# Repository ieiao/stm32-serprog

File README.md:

# STM32-serprog

## 概述

本项目是flashrom工具serprog编程器的一种实现，参考了[dword1511/stm32-vserprog](https://github.com/dword1511/stm32-vserprog)中v3版本电路原理图，增加了电平转换芯片用来同时支持1.8V和3.3V的spi flash，可以直接使用该仓库中的代码，经测试可以正常工作，PCB效果图如下。

## Changelog

* v0.2 (该版本未发板验证，不过原理图整体改动不大，应该没有问题)
    * 删除了多余的测试点
    * 将txs0108修改为txs0104/txb0104，节约成本

* v0.1
    * 第一个版本，已打板验证

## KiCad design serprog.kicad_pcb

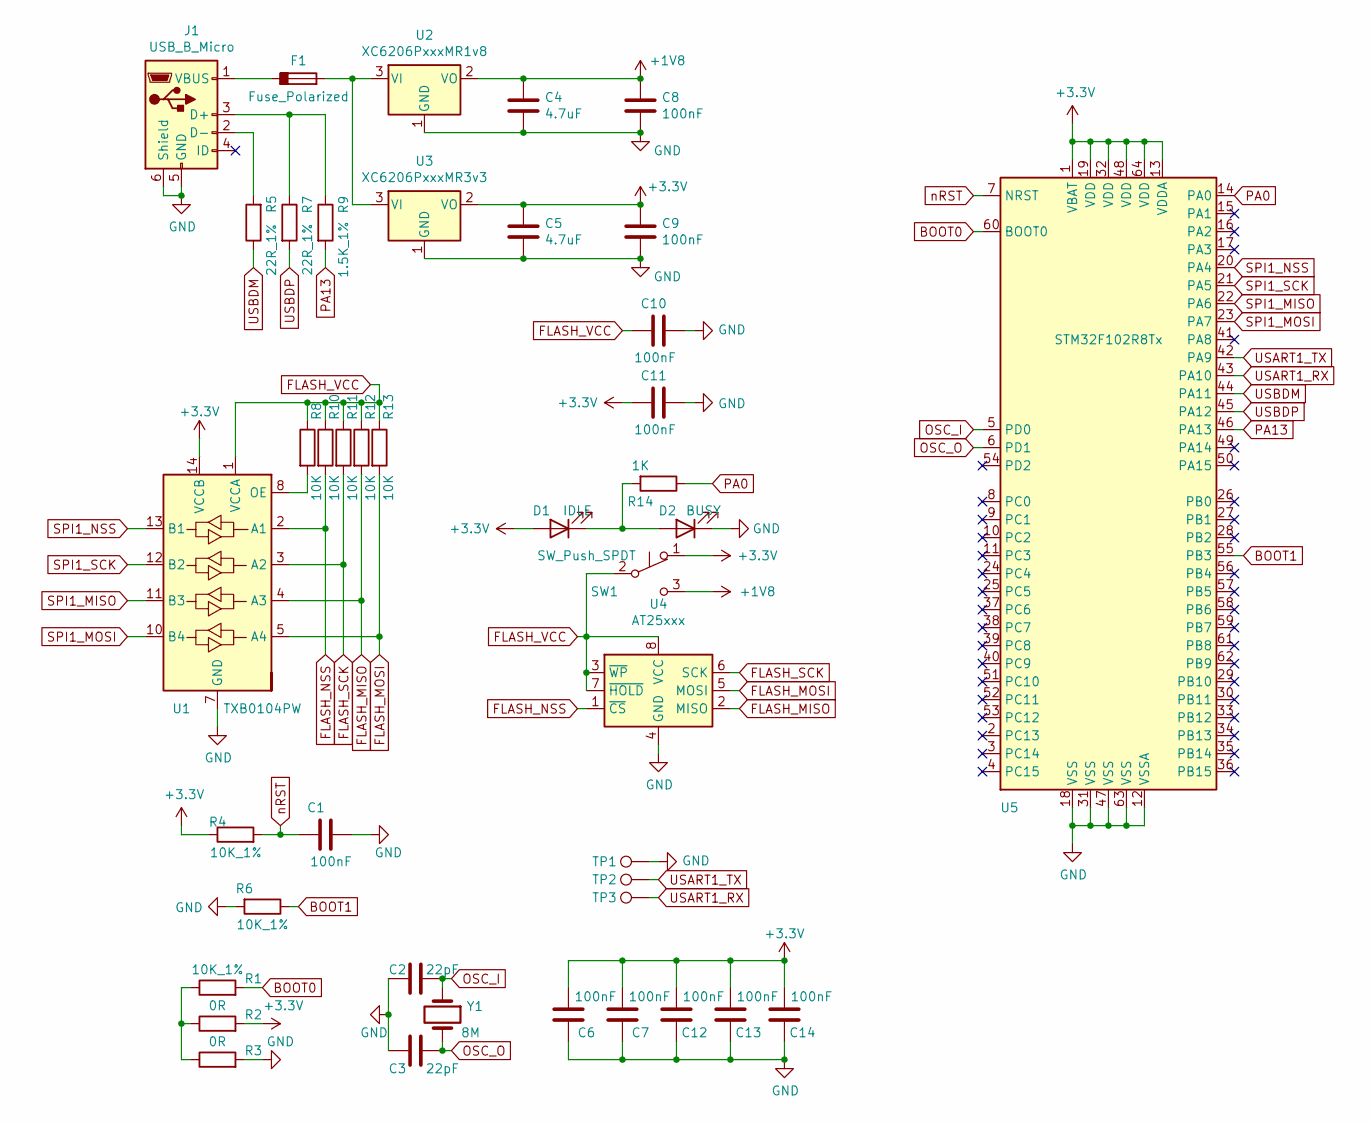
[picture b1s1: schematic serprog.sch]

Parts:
C1, C6, C7, C8, C9, C10, C11, C12, C13, C14: 100nF; C_0603_1608Metric
C2, C3: 22pF; C_0603_1608Metric
C4, C5: 4.7uF; C_0603_1608Metric
D1: IDLE; LED_0603_1608Metric
D2: BUSY; LED_0603_1608Metric
F1: Fuse_Polarized; Fuse_1210_3225Metric
J1: USB_B_Micro; USB_Micro-B_Molex-105017-0001
R1, R4, R6: 10K_1%; R_0603_1608Metric
R2, R3: 0R; R_0603_1608Metric
R5, R7: 22R_1%; R_0603_1608Metric
R8, R10, R11, R12, R13: 10K; R_0603_1608Metric
R9: 1.5K_1%; R_0603_1608Metric
R14: 1K; R_0603_1608Metric
SW1: SW_Push_SPDT; SW-DIP-3
TP1: GND; TestPoint_Pad_D1.0mm
TP2: TX; TestPoint_Pad_D1.0mm
TP3: RX; TestPoint_Pad_D1.0mm
U1: TXB0104PW; TSSOP-14_4.4x5mm_P0.65mm
U2: XC6206PxxxMR1v8; SOT-23
U3: XC6206PxxxMR3v3; SOT-23
U4: AT25xxx; DIP-8_W7.62mm
U5: STM32F102R8Tx; LQFP-64_10x10mm_P0.5mm
Y1: 8M; Crystal_HC49-4H_Vertical

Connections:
+1V8: C4.1, C8.1, SW1.3 (C), U2.2 (VO)
+3V3: C5.1, C6.1, C7.1, C9.1, C11.1, C12.1, C13.1, C14.1, D1.2 (A), R2.2, R4.1, SW1.1 (A), U1.14 (VCCB), U3.2 (VO), U5.1 (VBAT), U5.13 (VDDA), U5.19 (VDD), U5.32 (VDD), U5.48 (VDD), U5.64 (VDD)
BOOT0: R1.2, U5.60 (BOOT0)
BOOT1: R6.1, U5.55 (PB3)
FLASH_MISO: R12.2, U1.4 (A3), U4.2 (MISO)
FLASH_MOSI: R13.2, U1.5 (A4), U4.5 (MOSI)
FLASH_NSS: R10.2, U1.2 (A1), U4.1 (~CS)
FLASH_SCK: R11.2, U1.3 (A2), U4.6 (SCK)
FLASH_VCC: C10.1, R8.1, R10.1, R11.1, R12.1, R13.1, SW1.2 (B), U1.1 (VCCA), U4.3 (~WP), U4.7 (~HOLD), U4.8 (VCC)
GND: C1.2, C2.2, C3.2, C4.2, C5.2, C6.2, C7.2, C8.2, C9.2, C10.2, C11.2, C12.2, C13.2, C14.2, D2.1 (K), J1.5 (GND), J1.6 (Shield), R3.2, R6.2, TP1.1, U1.7 (GND), U2.1 (GND), U3.1 (GND), U4.4 (GND), U5.12 (VSSA), U5.18 (VSS), U5.31 (VSS), U5.47 (VSS), U5.63 (VSS); also elsewhere on the board
unnamed: D1.1 (K), D2.2 (A), R14.2
unnamed: F1.1, J1.1 (VBUS)
unnamed: F1.2, U2.3 (VI), U3.3 (VI)
unnamed: J1.2 (D-), R5.2
unnamed: J1.3 (D+), R7.1, R9.1
unnamed: R1.1, R2.1, R3.1
unnamed: R8.2, U1.8 (OE)
OSC_I: C2.1, U5.5 (PD0), Y1.1
OSC_O: C3.1, U5.6 (PD1), Y1.2
PA0: R14.1, U5.14 (PA0)
PA13: R9.2, U5.46 (PA13)
SPI1_MISO: U1.11 (B3), U5.22 (PA6)
SPI1_MOSI: U1.10 (B4), U5.23 (PA7)
SPI1_NSS: U1.13 (B1), U5.20 (PA4)
SPI1_SCK: U1.12 (B2), U5.21 (PA5)
USART1_RX: TP3.1, U5.43 (PA10); also elsewhere on the board
USART1_TX: TP2.1, U5.42 (PA9); also elsewhere on the board
USBDM: R5.1, U5.44 (PA11)
USBDP: R7.2, U5.45 (PA12)
nRST: C1.1, R4.2, U5.7 (NRST)

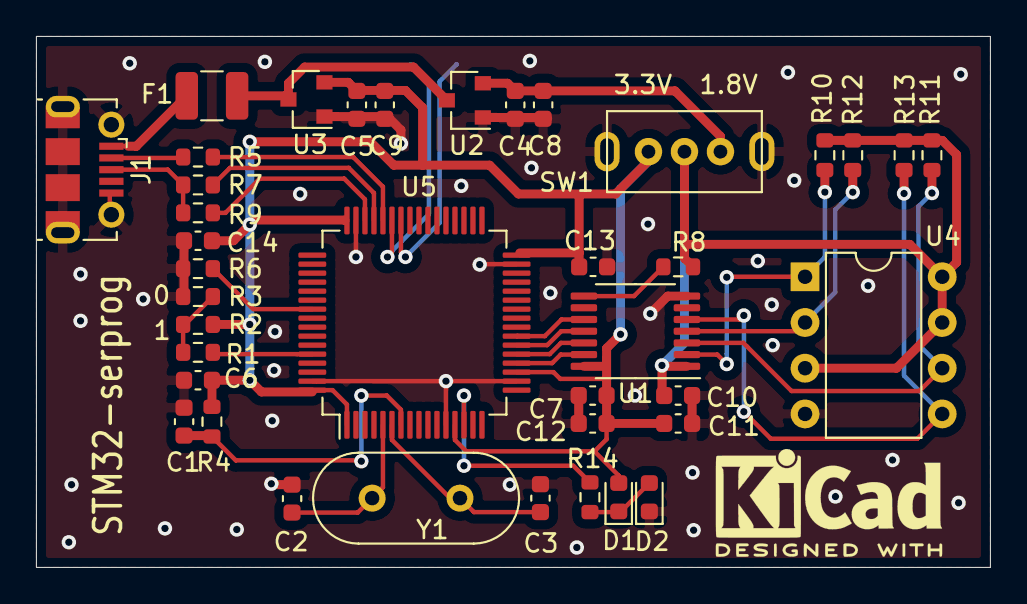
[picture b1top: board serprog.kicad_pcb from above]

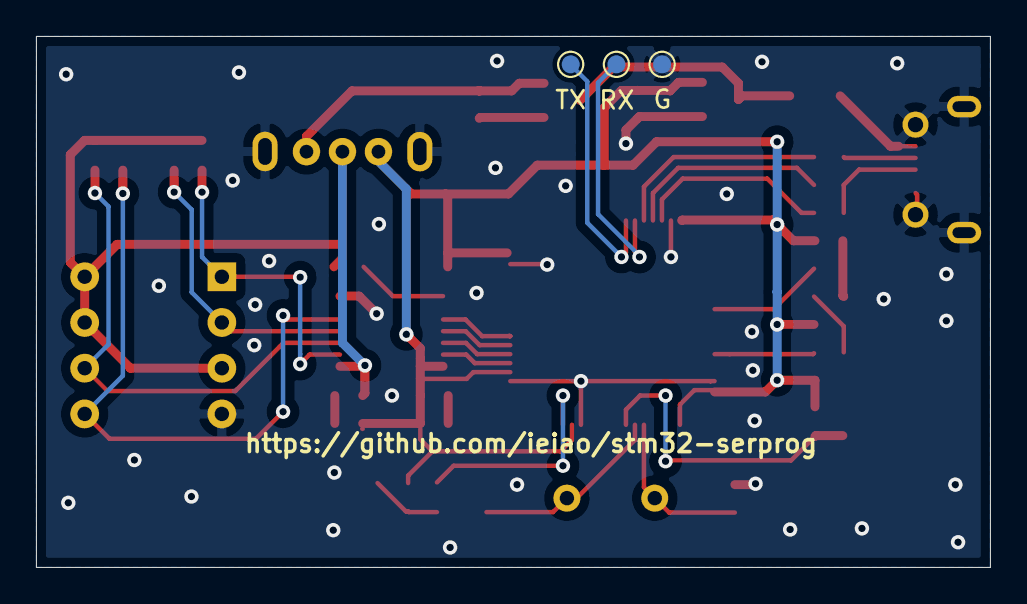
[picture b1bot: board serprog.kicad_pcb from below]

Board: 2 copper layers, 53.0 x 29.5 mm, 42 parts (3 on the bottom side), 30 nets.

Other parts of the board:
G: GND; TestPoint_Pad_D1.0mm
RX: RX; TestPoint_Pad_D1.0mm
TX: TX; TestPoint_Pad_D1.0mm

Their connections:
GND: G.1; also elsewhere on the board
USART1_RX: RX.1; also elsewhere on the board
USART1_TX: TX.1; also elsewhere on the board

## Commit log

2021-05-04 fist version
2021-05-09 v0.1
2021-05-16 v0.2
2021-05-22 fix url issue
